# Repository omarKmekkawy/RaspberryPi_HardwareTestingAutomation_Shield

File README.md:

# RaspberryPi_HardwareTestingAutomation_Shield
A Raspberry Pi Shield for Hardware Testing Automation

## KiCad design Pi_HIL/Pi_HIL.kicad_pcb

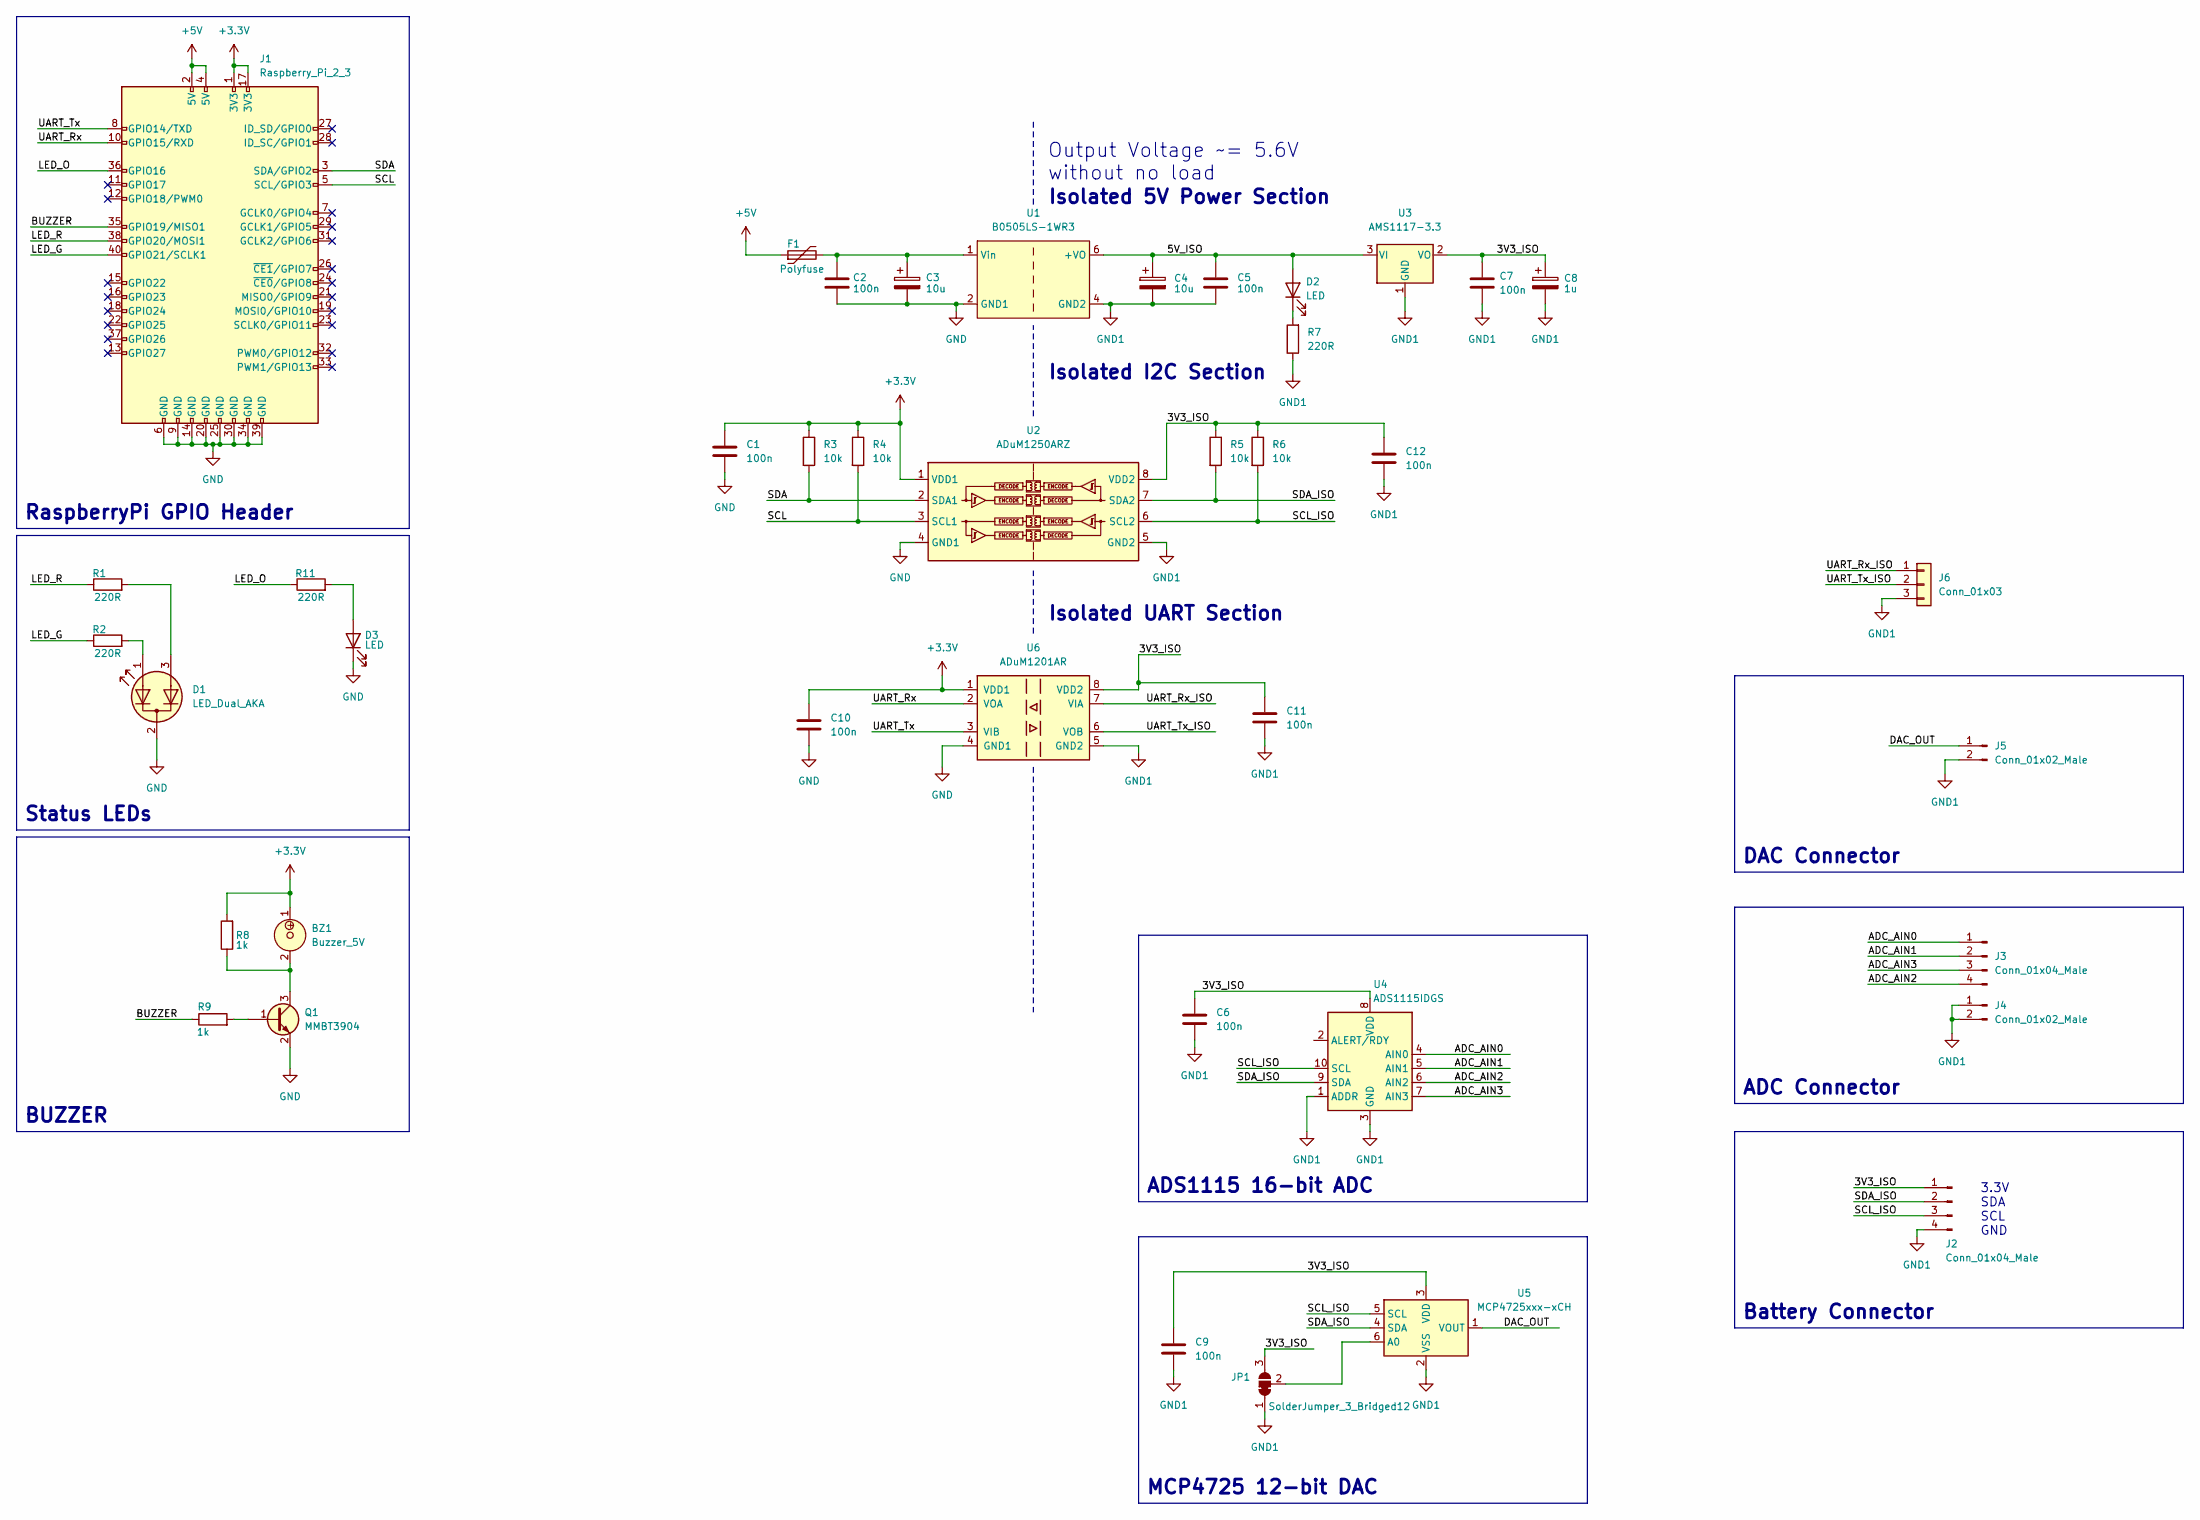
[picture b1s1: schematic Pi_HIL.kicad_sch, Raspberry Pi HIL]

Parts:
BZ1: Buzzer_5V; MagneticBuzzer_ProSignal_ABT-410-RC
C1, C2, C5, C6, C7, C9, C10, C11, C12: 100n; C_0805_2012Metric
C3, C4: 10u; CP_Radial_D4.0mm_P1.50mm
C8: 1u; CP_Radial_D4.0mm_P1.50mm
D1: LED_Dual_AKA; LED_D5.0mm-3_CC
D2, D3: LED; LED_0805_2012Metric
F1: Polyfuse; Fuse_1210_3225Metric_Pad1.42x2.65mm_HandSolder
J1: Raspberry_Pi_2_3; PinHeader_2x20_P2.54mm_Vertical
J2, J3: Conn_01x04_Male; PinHeader_1x04_P2.54mm_Vertical
J4, J5: Conn_01x02_Male; PinHeader_1x02_P2.54mm_Vertical
J6: Conn_01x03; PinHeader_1x03_P2.54mm_Vertical
JP1: SolderJumper_3_Bridged12; SolderJumper-3_P1.3mm_Bridged2Bar12_RoundedPad1.0x1.5mm
Q1: MMBT3904; SOT-23
R1, R2, R7, R11: 220R; R_0603_1608Metric
R3, R4, R5, R6: 10k; R_0603_1608Metric
R8, R9: 1k; R_0603_1608Metric
U1: B0505LS-1WR3; Converter_DCDC_TRACO_TMR-1-xxxx_Single_THT
U2: ADuM1250ARZ; SOIC-8_3.9x4.9mm_P1.27mm
U3: AMS1117-3.3; SOT-223-3_TabPin2
U4: ADS1115IDGS; TSSOP-10_3x3mm_P0.5mm
U5: MCP4725xxx-xCH; SOT-23-6
U6: ADuM1201AR; SOIC-8_3.9x4.9mm_P1.27mm

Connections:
+3.3V: BZ1.1, C1.1, C10.1, J1.1 (3V3), J1.17 (3V3), R3.1, R4.1, R8.2, U2.1 (VDD1), U6.1 (VDD1)
+5V: F1.1, J1.2 (5V), J1.4 (5V)
/3V3_ISO: C6.1, C7.1, C8.1, C9.1, C11.1, C12.1, J2.1, JP1.3 (B), R5.1, R6.1, U2.8 (VDD2), U3.2 (VO), U4.8 (VDD), U5.3 (VDD), U6.8 (VDD2)
/5V_ISO: C4.1, C5.1, D2.2 (A), U1.6 (+VO), U3.3 (VI)
/ADC_AIN0: J3.1, U4.4 (AIN0)
/ADC_AIN1: J3.2, U4.5 (AIN1)
/ADC_AIN2: J3.4, U4.6 (AIN2)
/ADC_AIN3: J3.3, U4.7 (AIN3)
/BUZZER: J1.35 (GPIO19/MISO1), R9.1
/DAC_OUT: J5.1, U5.1 (VOUT)
/LED_G: J1.40 (GPIO21/SCLK1), R2.1
/LED_O: J1.36 (GPIO16), R11.1
/LED_R: J1.38 (GPIO20/MOSI1), R1.1
/SCL: J1.5 (SCL/GPIO3), R4.2, U2.3 (SCL1)
/SCL_ISO: J2.3, R6.2, U2.6 (SCL2), U4.10 (SCL), U5.5 (SCL)
/SDA: J1.3 (SDA/GPIO2), R3.2, U2.2 (SDA1)
/SDA_ISO: J2.2, R5.2, U2.7 (SDA2), U4.9 (SDA), U5.4 (SDA)
/UART_Rx: J1.10 (GPIO15/RXD), U6.2 (VOA)
/UART_Rx_ISO: J6.1, U6.7 (VIA)
/UART_Tx: J1.8 (GPIO14/TXD), U6.3 (VIB)
/UART_Tx_ISO: J6.2, U6.6 (VOB)
GND: C1.2, C2.2, C3.2, C10.2, D1.2 (K), D3.1 (K), J1.6 (GND), J1.9 (GND), J1.14 (GND), J1.20 (GND), J1.25 (GND), J1.30 (GND), J1.34 (GND), J1.39 (GND), Q1.2 (E), U1.2 (GND1), U2.4 (GND1), U6.4 (GND1)
GND1: C4.2, C5.2, C6.2, C7.2, C8.2, C9.2, C11.2, C12.2, J2.4, J4.1, J4.2, J5.2, J6.3, JP1.1 (A), R7.1, U1.4 (GND2), U2.5 (GND2), U3.1 (GND), U4.1 (ADDR), U4.3 (GND), U5.2 (VSS), U6.5 (GND2)
unnamed: D1.1 (A1), R2.2
unnamed: D1.3 (A2), R1.2
unnamed: D2.1 (K), R7.2
unnamed: D3.2 (A), R11.2
unnamed: JP1.2 (C), U5.6 (A0)
unnamed: Q1.1 (B), R9.2
unnamed: BZ1.2, Q1.3 (C), R8.1
unnamed: C2.1, C3.1, F1.2, U1.1 (Vin)

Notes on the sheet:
RaspberryPi GPIO Header
Isolated I2C Section
Battery Connector
Output Voltage ~= 5.6V without no load
Isolated UART Section
3.3V SDA SCL GND
ADS1115 16-bit ADC
Status LEDs
ADC Connector
DAC Connector
MCP4725 12-bit DAC
Isolated 5V Power Section
BUZZER

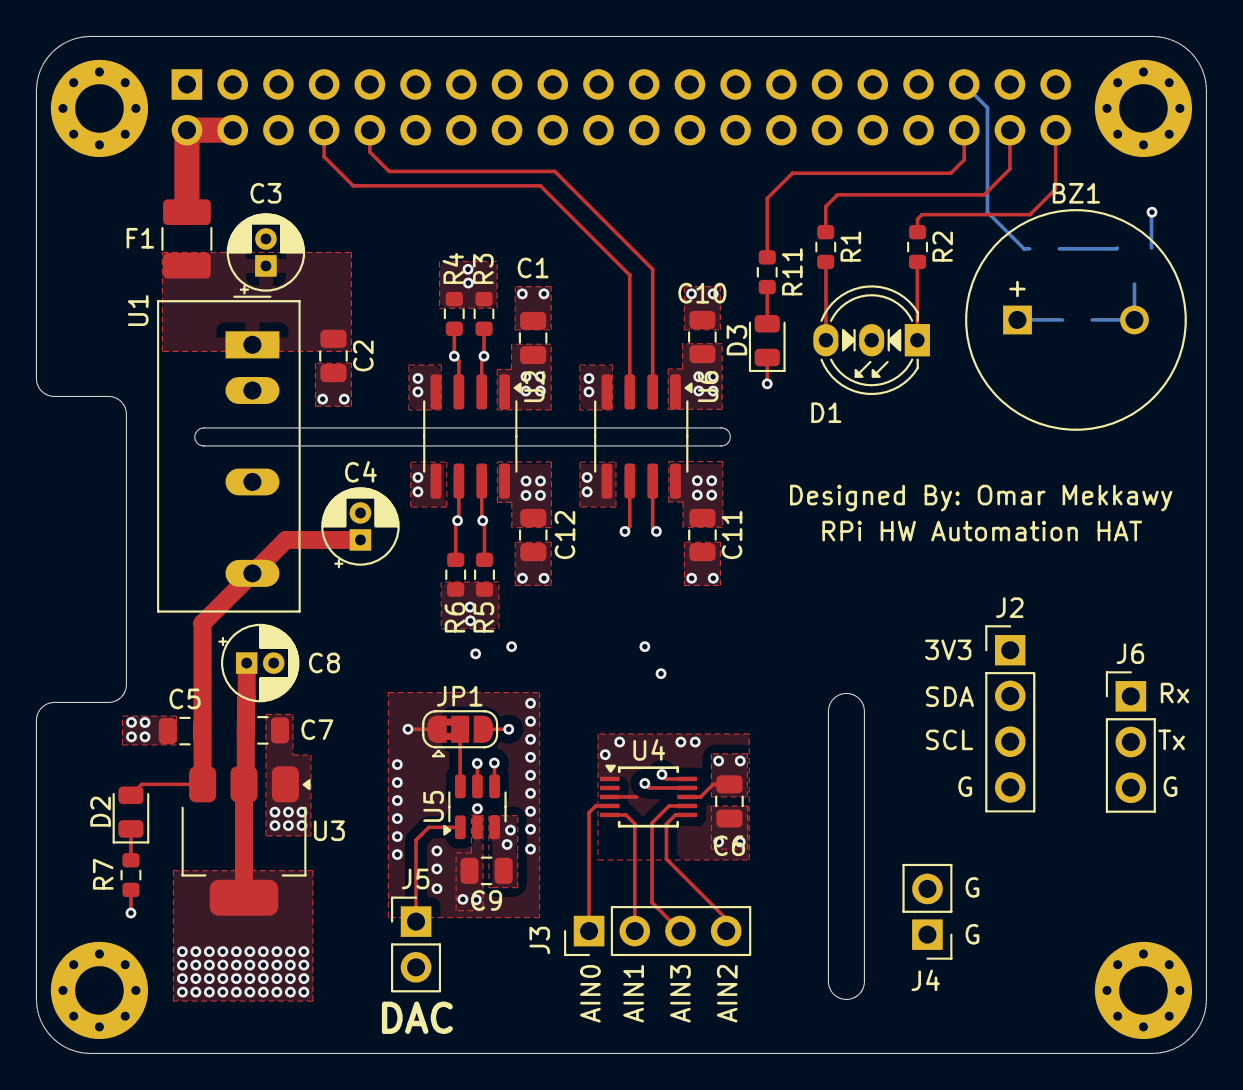
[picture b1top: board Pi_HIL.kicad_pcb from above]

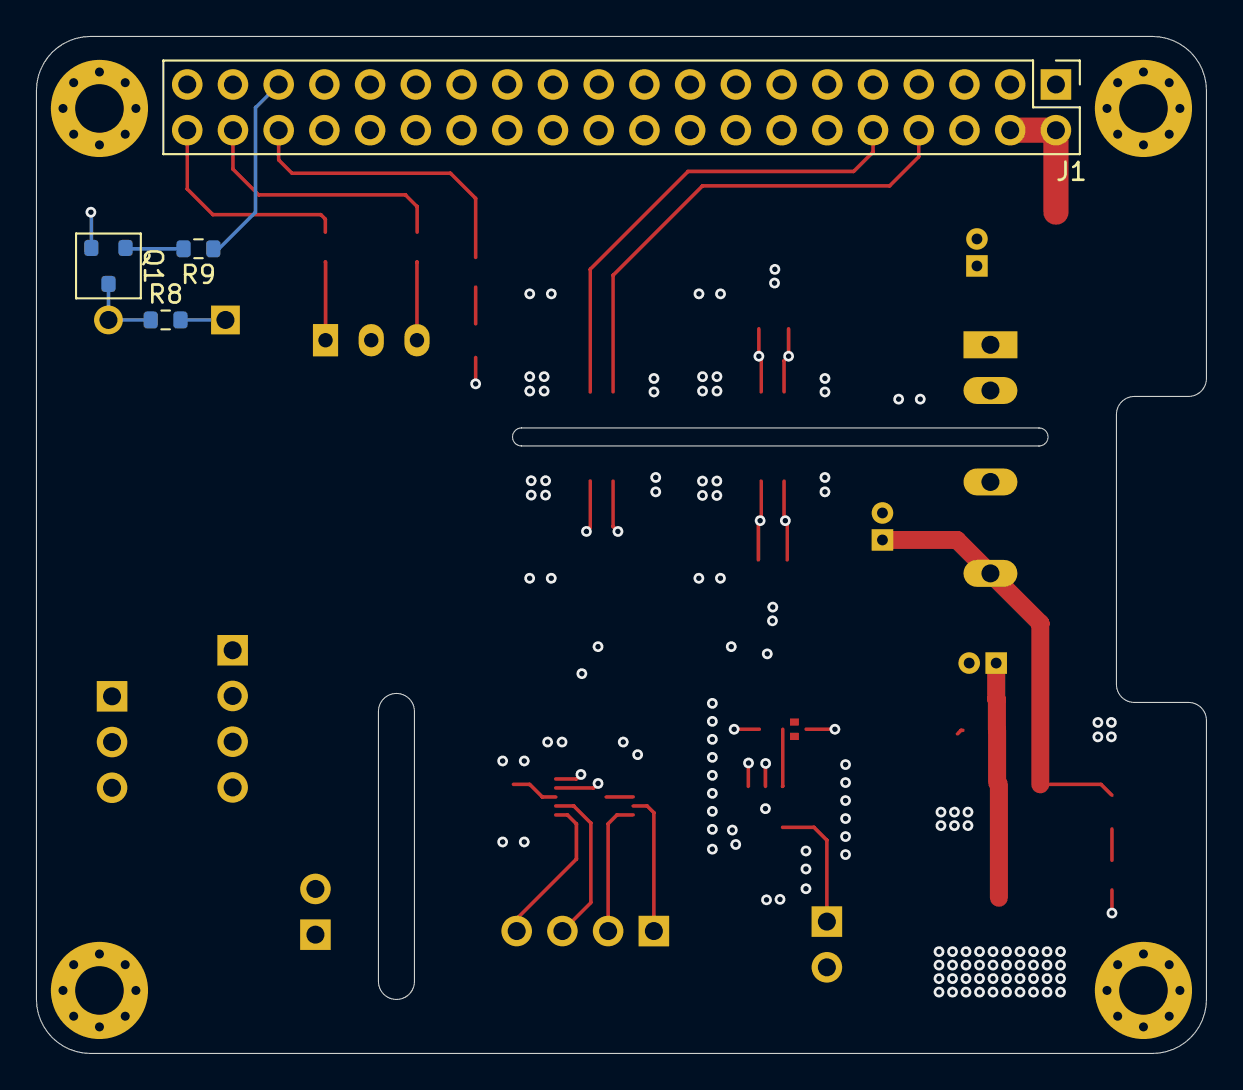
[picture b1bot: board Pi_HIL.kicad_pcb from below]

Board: 4 copper layers, 65.0 x 56.5 mm, 41 parts (4 on the bottom side), 31 nets.

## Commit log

2024-08-26 Added .ignore file for kicad
2024-08-26 Added ~Pi_HIL.kicad_sch.lck to .gitignore
2024-08-26 Initial commit for the Kicad project
2024-08-29 Updated Layout + Schematic
2024-08-29 Updated Layout, added UART + I2C headers
2024-08-30 Added schematic as a PDF file
2024-08-30 Connected LED D3 to GPIO 16
